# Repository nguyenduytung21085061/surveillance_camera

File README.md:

# 📷 Smart Home Surveillance Camera System

🇺🇸 English | 🇻🇳 [Vietnamese](README_vi.md)

---

## 📌 Project Status

This project is currently in the **research and development stage**.  
The goal is to develop a real product for **home use**, testing system stability, performance, and usability in real-world conditions.

---

## 🎯 Project Goal

Build a **low-cost smart home surveillance system** that can:

- Detect when someone stands in front of the house gate
- Notify family members inside the house in real time
- Run AI detection on an embedded device

In addition, the Camera Node is designed so it can be developed into an **independent smart door camera product**, which can:

- Be mounted in front of an apartment or house door
- Monitor visitors in real time
- Recognize whether the person is a family member or just detect unknown people
- Work as a standalone smart security device

---

## 🧱 System Architecture

The system is divided into **two main nodes**:

---

## 1️⃣ Camera Node

Main task: Monitor the front gate and detect people.

### Hardware

- Embedded board: Luckfox Pico (RV1103G1)
- USB Camera
- USB WiFi dongle (mainly for SSH development)
- Real-time display screen

### Why Luckfox Pico?

- Powerful enough to run person detection models
- Small size, low power
- Suitable for edge AI applications

### Functions

- Capture video from USB camera
- Run AI model to detect people
- Display real-time video
- Send notification signal to Notice Node

---

## 2️⃣ Notice Node

Main task: Notify people inside the house.

### Hardware

- MCU: STM32F103RCT6
- Audio amplifier (I2S output)
- Speaker module
- Wireless communication module: HC-12

### Functions

- Receive signal from Camera Node
- Play voice/audio alert
- Can be placed in kitchen, bedroom, etc.

---

## 📡 Communication

Camera Node communicates with Notice Node using:

- HC-12 wireless serial module
- Low cost
- Long range
- Simple UART interface

---

## 🛠 Technologies Used

- Embedded Linux on Luckfox Pico
- STM32 HAL firmware (C language)
- UART wireless communication
- AI person detection model (YOLO / RKNN planned)

---

## 📅 Project Progress

| No | Task | Status | Completion Date |
|----|------|--------|----------------|
| 1 | Read USB WiFi | ✅ Done | 24/01/2026 |
| 2 | Interface TFT display | ✅ Done | 25/01/2026 |
| 3 | Read USB camera | ✅ Done | 26/01/2026 |
| 4 | Stream USB camera on TFT | ✅ Done | 28/01/2026 |
| 5 | Add Mobile OpenCV on Luckfox Pico | ✅ Done | 29/01/2026 |
| 6 | Fit stream size from 160x120 → 160x128 on TFT | ✅ Done | 29/01/2026 |
| 7 | Run RKNN on Luckfox Pico | ✅ Done | 05/02/2026 |
| 8 | Load YOLOv5 model to detect person | ✅ Done | 07/02/2026 |
| 9 | Add confidence score on TFT | ✅ Done | 08/01/2026 |
|10 | Research USB hub expansion for Luckfox Pico | ✅ Done | 11/01/2026 |
|11 | Draw USB hub schematic for Camera Node | ✅ Done | 06/04/2026 |
|12 | Design PCB for Camera Node | ⏳ Pending | — |
|13 | Test STM32F103RCT6 board | ✅ Done | 15/01/2026 |
|14 | Test HC-12 communication between Luckfox Pico and STM32F103RCT6 | ✅ Done | 17/01/2026 |
|15 | Develop I2S audio with amplifier & speaker | ✅ Done| 22/02/2026 |
|16 | Full test: Person detection → Notice Node → Speaker alert | ⏳ Pending | — |
|17 | Research schematic for Notice Node | ⏳ Pending | — |
|18 | System evaluation testing | ⏳ Pending | — |
|19 | Upgrade TFT screen to larger display | ✅ Done | 03/04/2026 |
|20 | Research face embedding on Luckfox Pico | ⏳ Pending | — |
|21 | Develop standalone Camera Node product | ⏳ Pending | — |
|22 | Research mobile monitoring communication system | ⏳ Pending | — |

---

## 👨‍💻 Author

Nguyễn Duy Tùng  
Embedded Systems & IoT Developer  

---

⭐ If you like this project, please give it a star!

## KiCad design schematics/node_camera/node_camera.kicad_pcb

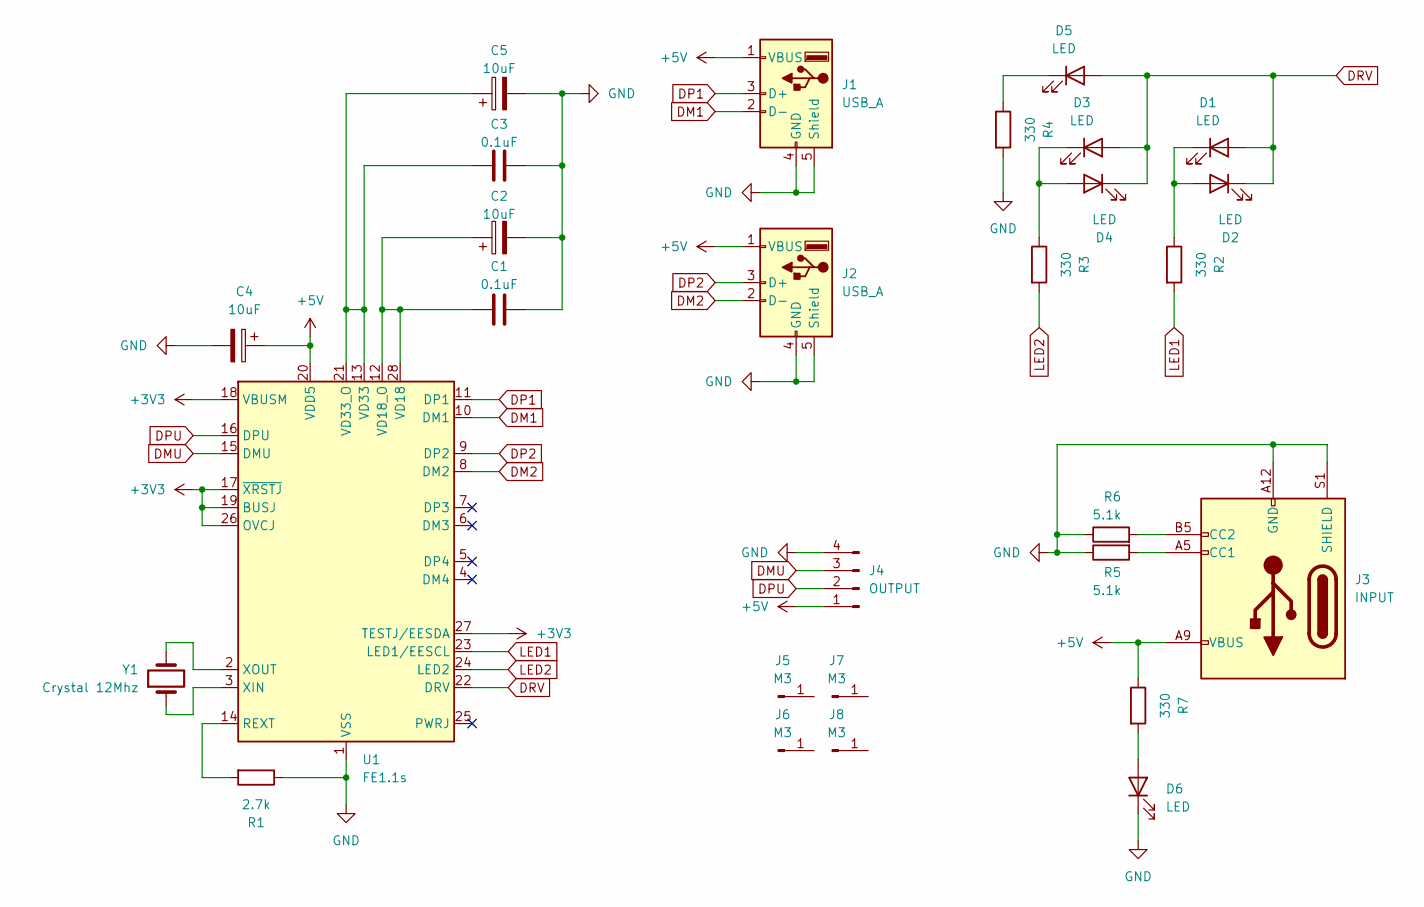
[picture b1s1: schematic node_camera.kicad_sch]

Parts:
C1, C3: 0.1uF; C_Disc_D3.0mm_W1.6mm_P2.50mm
C2, C4, C5: 10uF; CP_Radial_D4.0mm_P2.00mm
D1, D2, D3, D4, D5, D6: LED; LED_D3.0mm
J1, J2: USB_A; USB_A_Stewart_SS-52100-001_Horizontal
J3: INPUT; USB_C_Receptacle_GCT_USB4125-xx-x-0190_6P_TopMnt_Horizontal
J4: OUTPUT; PinSocket_1x04_P2.54mm_Vertical
J5, J6, J7, J8: M3; MountingHole_3.2mm_M3_Pad_Via
R1: 2.7k; R_Axial_DIN0207_L6.3mm_D2.5mm_P7.62mm_Horizontal
R2, R3, R4, R7: 330; R_Axial_DIN0207_L6.3mm_D2.5mm_P7.62mm_Horizontal
R5, R6: 5.1k; R_Axial_DIN0207_L6.3mm_D2.5mm_P7.62mm_Horizontal
U1: FE1.1s; SSOP-28_3.9x9.9mm_P0.635mm
Y1: Crystal 12Mhz; Crystal_HC49-4H_Vertical

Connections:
+3V3: U1.17 (~XRSTJ), U1.18 (VBUSM), U1.19 (BUSJ), U1.26 (OVCJ), U1.27 (TESTJ/EESDA)
+5V: C4.1, J1.1 (VBUS), J2.1 (VBUS), J3.A9 (VBUS), J3.B9 (VBUS), J4.1, R7.1, U1.20 (VDD5)
DM1: J1.2 (D-), U1.10 (DM1)
DM2: J2.2 (D-), U1.8 (DM2)
DMU: J4.3, U1.15 (DMU)
DP1: J1.3 (D+), U1.11 (DP1)
DP2: J2.3 (D+), U1.9 (DP2)
DPU: J4.2, U1.16 (DPU)
DRV: D1.2 (A), D2.1 (K), D3.2 (A), D4.1 (K), D5.2 (A), U1.22 (DRV)
GND: C1.2, C2.2, C3.2, C4.2, C5.2, D6.1 (K), J1.4 (GND), J1.5 (Shield), J2.4 (GND), J2.5 (Shield), J3.A12 (GND), J3.B12 (GND), J3.S1 (SHIELD), J4.4, R1.1, R4.2, R5.1, R6.1, U1.1 (VSS)
LED1: R2.2, U1.23 (LED1/EESCL)
LED2: R3.2, U1.24 (LED2)
unnamed: D1.1 (K), D2.2 (A), R2.1
unnamed: D3.1 (K), D4.2 (A), R3.1
unnamed: D5.1 (K), R4.1
unnamed: D6.2 (A), R7.2
unnamed: J3.A5 (CC1), R5.2
unnamed: J3.B5 (CC2), R6.2
unnamed: R1.2, U1.14 (REXT)
unnamed: C1.1, C2.1, U1.12 (VD18_O), U1.28 (VD18)
unnamed: C3.1, C5.1, U1.13 (VD33), U1.21 (VD33_O)
unnamed: U1.3 (XIN), Y1.1
unnamed: U1.2 (XOUT), Y1.2

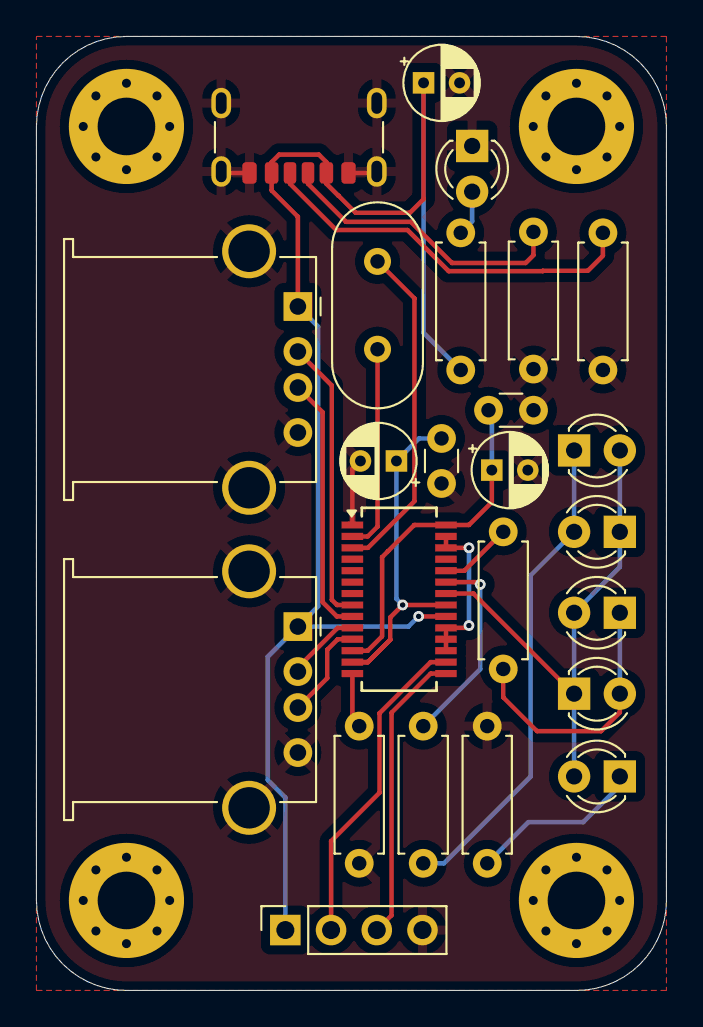
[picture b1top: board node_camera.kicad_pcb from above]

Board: 2 copper layers, 35.0 x 53.0 mm, 28 parts (0 on the bottom side), 23 nets.

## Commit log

2026-01-24 create node camera
2026-01-24 create class gpio is export unexport direction
2026-01-25 complited on gpio driver not test function
2026-01-25 driver spi on linux
2026-01-25 .gitingore
2026-01-25 new commit refesh project
2026-01-25 repair spi, gpio, st7735s
2026-01-25 finish oop on project
2026-01-25 repair code not init tft
2026-01-25 turn oon printf is not debug
2026-01-29 add opencv-mobile on luckfox-pico
2026-01-29 fit size stream on tft from 160x120 to 160x128
2026-02-05 add rknn model zoo yolov5 and utils
2026-02-06 add library 3rdparty luckfox pico
2026-02-06 repair source yolov5 on luckfox pico
2026-02-06 remove main.cc on node_camera/yolov5/src/
2026-02-06 repair source uitls on luckfox pico
2026-02-06 remove CMake
2026-02-07 resource opencv mobile and rknn in luckfox pico
2026-02-07 add jpeg turbo, librga, stb image, utils, postprocess, yolov5 and model human detect
2026-02-07 fix type malloc function from (void *) to (unsigned char *)
2026-02-07 fix constructor goto
2026-02-07 fix type variable data from (void *) to (const char *) and add return -1 on function get_image_Size
2026-02-07 rename file c to cc
2026-02-07 fix rename
2026-02-07 fix lable out on block
2026-02-07 success load model yolov5 rknn on luckfox pico
2026-02-07 remove frame timing and FPS limiting from main loop
2026-02-08 add Confidence score on tft 1.8 inch
2026-02-17 Fix flickering bounding boxes by caching last YOLO detections
2026-02-20 upload description project
2026-02-20 add schedule project
2026-02-22 create project stm32 on node notice
2026-02-22 update time on project stm32 test amplifier
2026-02-22 test communication node camera and node node notice on hc12
2026-02-22 update readme vi
2026-02-23 show file config
2026-02-24 hide json
2026-04-02 driver tft ili9341
2026-04-03 update stream tft ili9341
2026-04-06 Draw schematic and PCB USB hub usb ic fe1.1s
2026-04-06 Update schedule project
